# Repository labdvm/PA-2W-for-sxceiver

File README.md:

# PA-2W-for-sxceiver
# High Linearity Amplifier up to  2W for SXceiver or mini-HAT without PA on it. 
# You can Donate for better progress and support, https://www.paypal.com/donate/?hosted_button_id=WZ52L7DWVVQ28

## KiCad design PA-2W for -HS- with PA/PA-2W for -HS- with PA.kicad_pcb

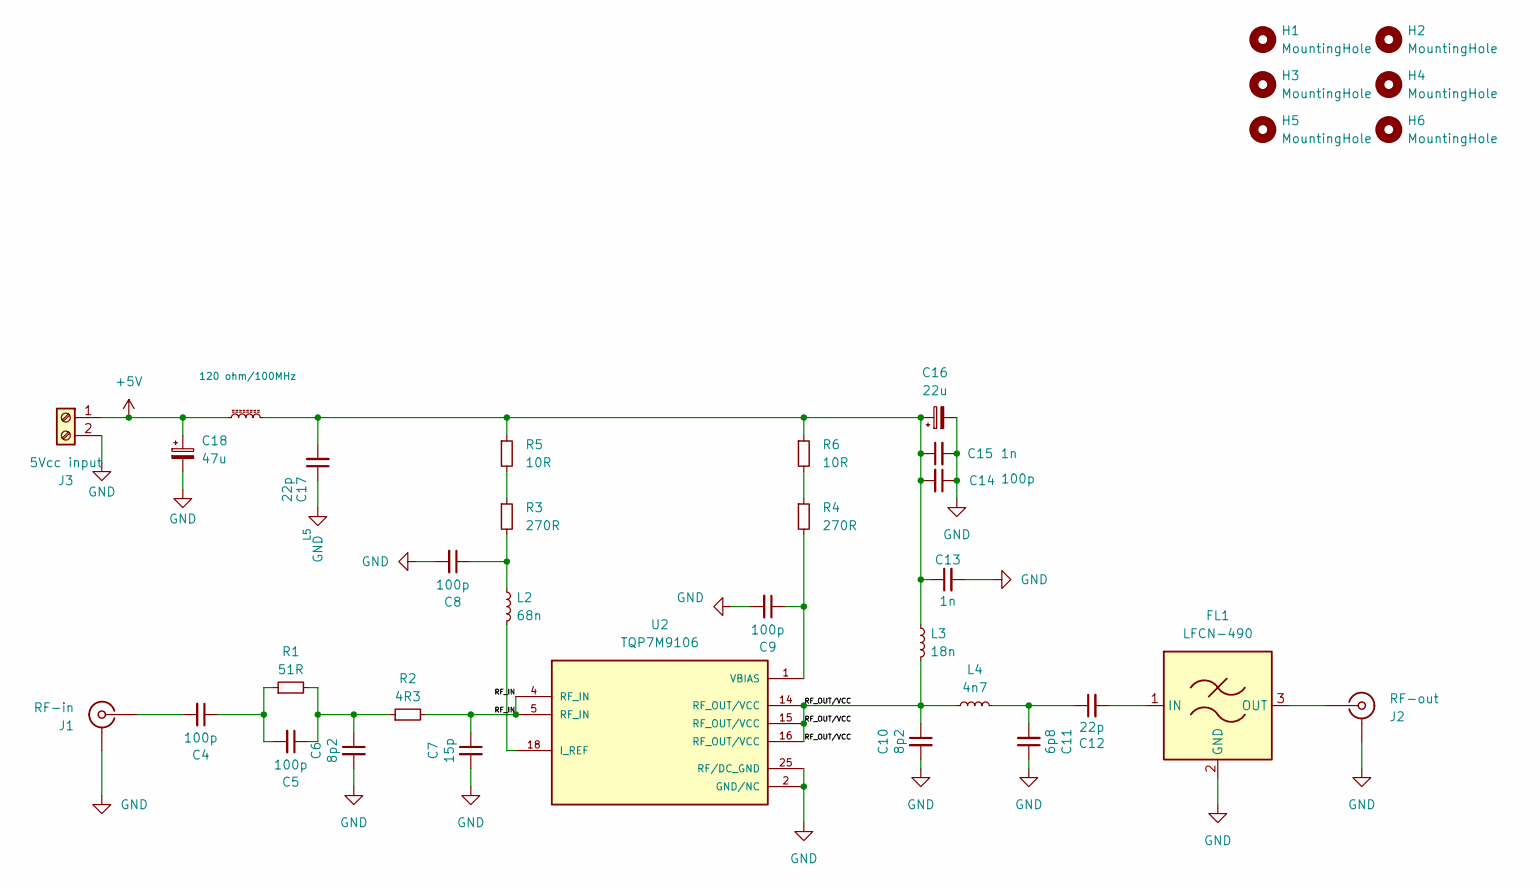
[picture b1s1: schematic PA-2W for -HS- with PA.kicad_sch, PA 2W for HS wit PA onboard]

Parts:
C4, C5, C8, C9, C14: 100p; C_0603_1608Metric; DigiKey Part Number 311-3599-1-ND
C6, C10: 8p2; C_0603_1608Metric; DigiKey Part Number 311-3347-1-ND
C7: 15p; C_0603_1608Metric; DigiKey Part Number 13-AC0603FRNPO9BN150CT-ND
C11: 6p8; C_0603_1608Metric; DigiKey Part Number 311-3838-1-ND
C12: 22p; C_0603_1608Metric; DigiKey Part Number 311-3350-1-ND
C13, C15: 1n; C_0603_1608Metric; DigiKey Part Number 490-1451-1-ND
C16: 22u; CP_EIA-3528-15_AVX-H_HandSolder; DigiKey Part Number 478-1682-1-ND
C17: 22p; C_0805_2012Metric; DigiKey Part Number 311-4171-1-ND
C18: 47u; CP_EIA-3528-15_AVX-H_HandSolder; DigiKey Part Number 478-1718-1-ND
FL1: LFCN-490; Filter_Mini-Circuits_FV1206; DigiKey Part Number 3157-LFCN-490+CT-ND
H1, H2, H3, H4, H5, H6: MountingHole; MountingHole_2.2mm_M2_DIN965_Pad
J1: RF-in; SMA_Amphenol_132289_EdgeMount
J2: RF-out; SMA_Amphenol_132289_EdgeMount
J3: 5Vcc input; TerminalBlock_bornier-2_P5.08mm; DigiKey Part Number 277-12547-ND
L2: 68n; L_0603_1608Metric; DigiKey Part Number 490-15846-1-ND
L3: 18n; L_1008_2520Metric; DigiKey Part Number 535-AISC-1008HQ-18NG-TTR-ND
L4: 4n7; L_0603_1608Metric; DigiKey Part Number 490-LQW18AS4N7J00DCT-ND
L5: 120 ohm/100MHz; L_1206_3216Metric; DigiKey Part Number 240-2401-1-ND
R1: 51R; R_0603_1608Metric; DigiKey Part Number 541-51.0HCT-ND
R2: 4R3; R_0603_1608Metric; DigiKey Part Number 541-4.30HHCT-ND
R3, R4: 270R; R_0603_1608Metric; DigiKey Part Number 541-280HCT-ND
R5: 10R; R_0603_1608Metric; DigiKey Part Number 541-280HCT-ND
R6: 10R; R_0603_1608Metri; DigiKey Part Number 541-280HCT-ND
U2: TQP7M9106; QFN50P400X400X90-25N; DigiKey Part Number 2312-TQP7M9106CT-ND

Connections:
+5V: C18.1, J3.1, L5.1
/RF_IN: C7.1, R2.2, U2.4 (RF_IN), U2.5 (RF_IN)
/RF_OUT/VCC: C10.1, L3.2, L4.1, U2.14 (RF_OUT/VCC), U2.15 (RF_OUT/VCC), U2.16 (RF_OUT/VCC)
GND: C6.2, C7.2, C8.2, C9.2, C10.2, C11.1, C13.2, C14.1, C15.2, C16.2, C17.1, C18.2, FL1.2 (GND), FL1.4 (GND), H1.1, H2.1, H4.1, H6.1, J1.2 (Ext), J2.2 (Ext), J3.2, U2.2 (GND/NC), U2.3 (GND/NC), U2.6 (GND/NC), U2.7 (GND/NC), U2.8 (GND/NC), U2.9 (GND/NC), U2.10 (GND/NC), U2.11 (GND/NC), U2.12 (GND/NC), U2.13 (GND/NC), U2.17 (GND/NC), U2.19 (GND/NC), U2.20 (GND/NC), U2.21 (GND/NC), U2.22 (GND/NC), U2.23 (GND/NC), U2.24 (GND/NC), U2.25 (RF/DC_GND), U2.26 (RF/DC_GND), U2.27, U2.28, U2.29, U2.30, U2.31, U2.32, U2.33, U2.34, U2.35, U2.36, U2.37, U2.38, U2.39, U2.40, U2.41, U2.42
unnamed: C4.1, C5.2, R1.1
unnamed: C5.1, C6.1, R1.2, R2.1
unnamed: C8.1, L2.1, R3.2
unnamed: C11.2, C12.1, L4.2
unnamed: C13.1, C14.2, C15.1, C16.1, C17.2, L3.1, L5.2, R5.1, R6.1
unnamed: C12.2, FL1.1 (IN)
unnamed: FL1.3 (OUT), J2.1 (In)
unnamed: C4.2, J1.1 (In)
unnamed: R3.1, R5.2
unnamed: R4.1, R6.2
unnamed: L2.2, U2.18 (I_REF)
unnamed: C9.1, R4.2, U2.1 (VBIAS)

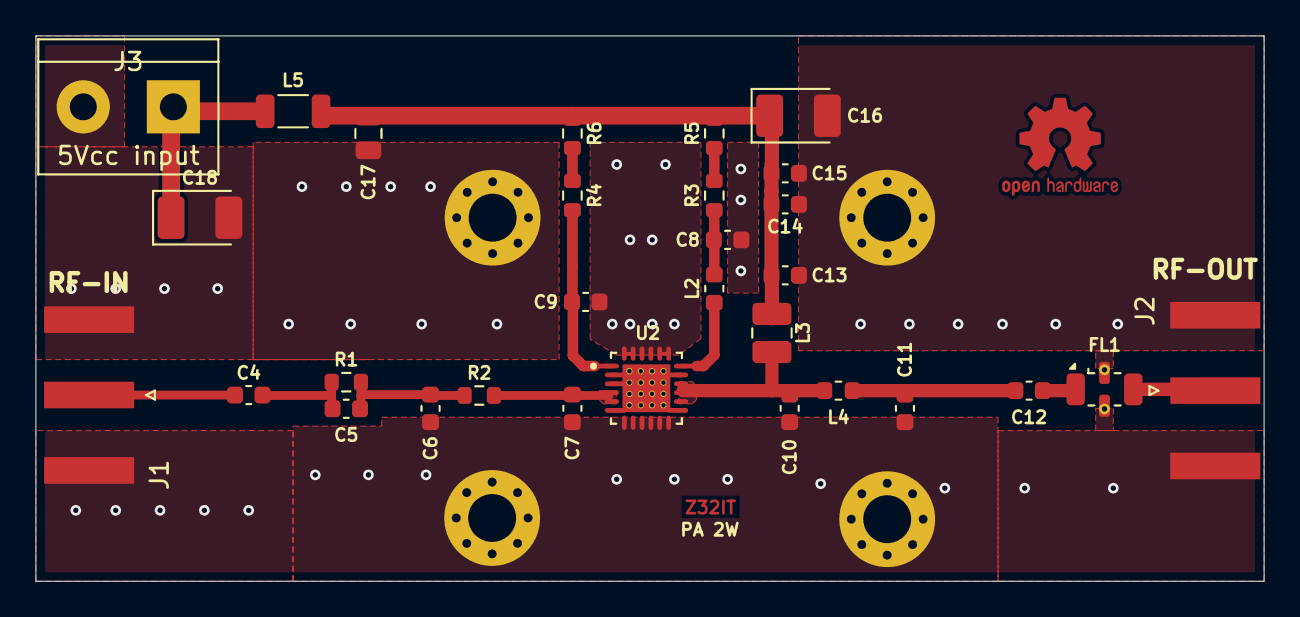
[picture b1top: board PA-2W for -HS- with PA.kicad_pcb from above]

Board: 2 copper layers, 69.2 x 30.8 mm, 34 parts (0 on the bottom side), 16 nets.

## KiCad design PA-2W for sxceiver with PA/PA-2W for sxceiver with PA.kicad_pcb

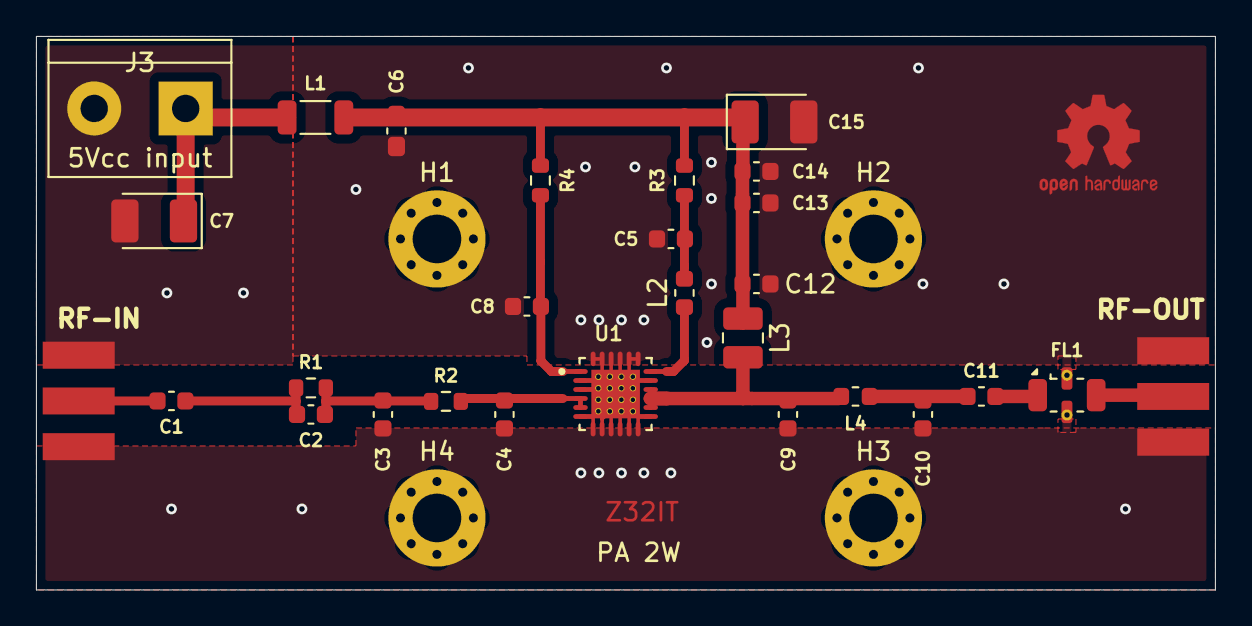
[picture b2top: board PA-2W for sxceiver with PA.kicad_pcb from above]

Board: 2 copper layers, 65.5 x 30.8 mm, 32 parts (0 on the bottom side), 15 nets.

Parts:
C1, C2, C5, C8, C13: 100p; C_0603_1608Metric
C3, C9: 8p2; C_0603_1608Metric
C4: 15p; C_0603_1608Metric
C6: 22p; C_0603_1608Metric_Pad1.08x0.95mm_HandSolder
C7: 47u; CP_EIA-3528-15_AVX-H_HandSolder
C10: 6p8; C_0603_1608Metric
C11: 22p; C_0603_1608Metric
C12, C14: 1n; C_0603_1608Metric
C15: 22u; CP_EIA-3528-15_AVX-H_HandSolder
FL1: LFCN-490; Filter_Mini-Circuits_FV1206
H1, H2, H3, H4: MountingHole_2.7mm_M2.5_Pad_Via
J1: SMA_RF IN; SMA_Edge_6.3mm
J2: SMA_RF OUT; SMA_Edge_6.3mm
J3: 5Vcc input; TerminalBlock_bornier-2_P5.08mm
L1: 120 ohm/100MHz; L_1206_3216Metric
L2: 68n; L_0603_1608Metric
L3: 18n; L_1008_2520Metric
L4: 4n7; L_0603_1608Metric
R1: 51R; R_0603_1608Metric
R2: 4R3; R_0603_1608Metric
R3, R4: 280R; R_0603_1608Metric
U1: TQP7M9106; QFN50P400X400X90-25N

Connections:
+5V: C7.1, J3.1, L1.1
/RF_IN: C4.1, R2.2
GND: C3.2, C4.2, C5.2, C6.1, C7.2, C8.2, C9.2, C10.1, C12.2, C13.1, C14.2, C15.2, FL1.2 (GND), FL1.4 (GND), H1.1, H2.2, H3.3, H4.4, J1.2 (Ext), J2.2 (Ext), J3.2, U1.2 (GND/NC), U1.3 (GND/NC), U1.6 (GND/NC), U1.7 (GND/NC), U1.8 (GND/NC), U1.9 (GND/NC), U1.10 (GND/NC), U1.11 (GND/NC), U1.12 (GND/NC), U1.13 (GND/NC), U1.17 (GND/NC), U1.19 (GND/NC), U1.20 (GND/NC), U1.21 (GND/NC), U1.22 (GND/NC), U1.23 (GND/NC), U1.24 (GND/NC), U1.25 (RF/DC_GND), U1.26 (RF/DC_GND)
unnamed: C1.1, C2.2, R1.1
unnamed: C2.1, C3.1, R1.2, R2.1
unnamed: C5.1, L2.1, R3.2
unnamed: U1.4 (RF_IN), U1.5 (RF_IN)
unnamed: C9.1, L3.2, L4.1, U1.14 (RF_OUT/VCC), U1.15 (RF_OUT/VCC), U1.16 (RF_OUT/VCC)
unnamed: C10.2, C11.1, L4.2
unnamed: C6.2, C12.1, C13.2, C14.1, C15.1, L1.2, L3.1, R3.1, R4.1
unnamed: C11.2, FL1.1 (IN)
unnamed: FL1.3 (OUT), J2.1 (In)
unnamed: C1.2, J1.1 (In)
unnamed: L2.2, U1.18 (I_REF)
unnamed: C8.1, R4.2, U1.1 (VBIAS)

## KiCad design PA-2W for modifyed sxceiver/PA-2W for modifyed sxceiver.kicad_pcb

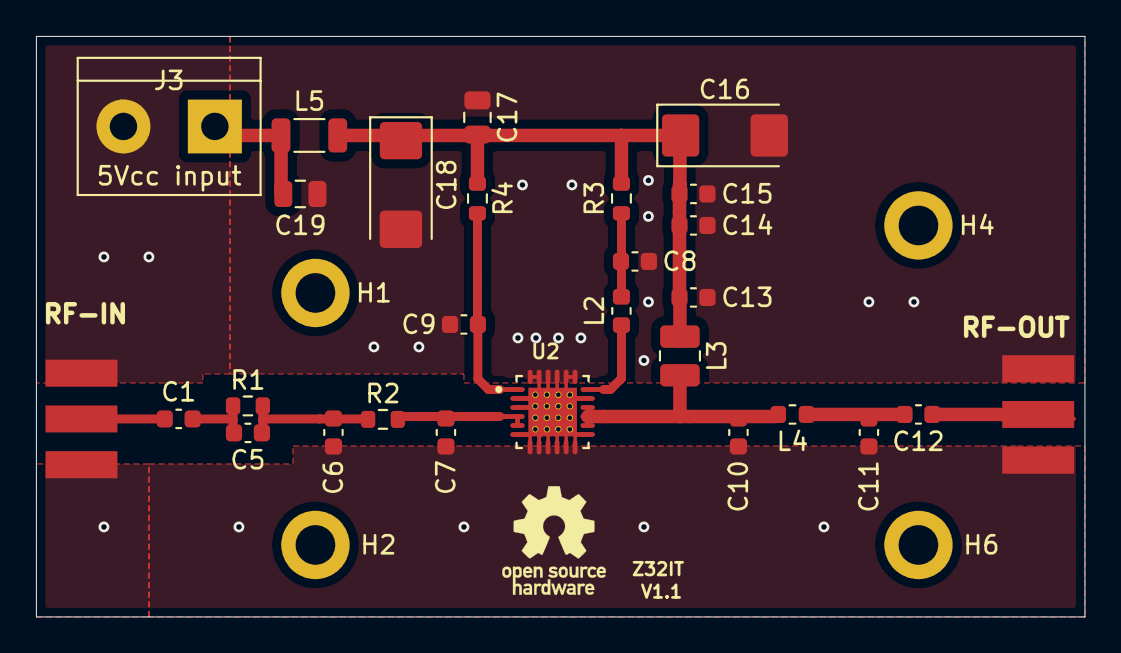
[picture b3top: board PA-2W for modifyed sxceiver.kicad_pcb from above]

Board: 2 copper layers, 58.2 x 32.2 mm, 32 parts (0 on the bottom side), 14 nets.

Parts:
C1, C5, C8, C9, C14: 100p; C_0603_1608Metric
C6, C10: 8p2; C_0603_1608Metric
C7: 15p; C_0603_1608Metric
C11: 6p8; C_0603_1608Metric
C12: 22p; C_0603_1608Metric
C13, C15: 1n; C_0603_1608Metric
C16, C18: 22u; CP_EIA-6032-28_Kemet-C
C17: 22p; C_0805_2012Metric
C19: 1u; C_0805_2012Metric
H1, H2, H4, H6: MountingHole; MountingHole_2.2mm_M2_DIN965_Pad
J1: SMA_RF IN; SMA_Edge_6.3mm
J2: SMA_RF OUT; SMA_Edge_6.3mm
J3: 5Vcc input; TerminalBlock_bornier-2_P5.08mm
L2: 68n; L_0603_1608Metric
L3: 18n; L_1008_2520Metric
L4: 4n7; L_0603_1608Metric
L5: 120 ohm/100MHz; L_1206_3216Metric
R1: 51R; R_0603_1608Metric
R2: 4R3; R_0603_1608Metric
R3, R4: 280R; R_0603_1608Metric
U2: TQP7M9106; QFN50P400X400X90-25N

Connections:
+5V: C19.2, J3.1, L5.1
/RF_IN: C7.1, R2.2
/RF_OUT/VCC: C10.1, L3.2, L4.1
GND: C6.2, C7.2, C8.1, C9.1, C10.2, C11.1, C13.2, C14.2, C15.2, C16.2, C17.1, C18.2, C19.1, J1.2 (Ext), J2.2 (Ext), J3.2, U2.2 (GND/NC), U2.3 (GND/NC), U2.6 (GND/NC), U2.7 (GND/NC), U2.8 (GND/NC), U2.9 (GND/NC), U2.10 (GND/NC), U2.11 (GND/NC), U2.12 (GND/NC), U2.13 (GND/NC), U2.17 (GND/NC), U2.19 (GND/NC), U2.20 (GND/NC), U2.21 (GND/NC), U2.22 (GND/NC), U2.23 (GND/NC), U2.24 (GND/NC), U2.25 (RF/DC_GND), U2.26 (RF/DC_GND)
unnamed: C1.1, C5.1, R1.1
unnamed: C5.2, C6.1, R1.2, R2.1
unnamed: U2.4 (RF_IN), U2.5 (RF_IN)
unnamed: C8.2, L2.1, R3.2
unnamed: U2.14 (RF_OUT/VCC), U2.15 (RF_OUT/VCC), U2.16 (RF_OUT/VCC)
unnamed: C11.2, C12.1, L4.2
unnamed: C13.1, C14.1, C15.1, C16.1, C17.2, C18.1, L3.1, L5.2, R3.1, R4.1
unnamed: C1.2, J1.1 (In)
unnamed: C12.2, J2.1 (In)
unnamed: C9.2, R4.2

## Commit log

2026-03-19 Update description of High Linearity Amplifier
2026-03-25 Update README to clarify amplifier specifications
2026-03-30 Add donation link to README
    Added donation link for project support.
